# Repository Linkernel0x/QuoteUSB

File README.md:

# QuoteUSB

A small 3-button USB MacroPad built for HackClub as a hardware experiment with the CH552G microcontroller

---

- **Microcontroller:** CH552G
- **Inputs:** 3 switches (Quote Generator 1, Quote Generator 2, Macro button)
- **Status:** Integrated LED indicator on keypress

For the full devlog and project history, check out [JOURNAL.md](JOURNAL.md).

### Firmware
1. Open `firmware/firmware.ino` in Arduino IDE
2. Select **CH552 Board** and upload method **USER CODE w/ 148B USB ram** using the ch55xduino core
3. Flash the CH552

### BOM
| Reference   | Qty | Value    | Footprint                                            | Datasheet                                                                                        |
|:------------|:----|:---------|:-----------------------------------------------------|:-------------------------------------------------------------------------------------------------|
| C1,C2       | 2   | 100nf    | Capacitor\_SMD:C\_0805\_2012Metric                   | \~                                                                                               |
| D1          | 1   | LED      | LED\_SMD:LED\_0805\_2012Metric                       | \~                                                                                               |
| J1          | 1   | USB\_A   | Connector\_USB:USB\_A\_Molex\_48037-2200\_Horizontal | \~                                                                                               |
| R1          | 1   | 330R     | Resistor\_SMD:R\_0805\_2012Metric                    | \~                                                                                               |
| SW1,SW2,SW3 | 3   | SW\_Push | Button\_Switch\_SMD:SW\_SPST\_PTS645Sx43SMTR92       | \~                                                                                               |
| U1          | 1   | CH552G   | Package\_SO:SOIC-16\_3.9x9.9mm\_P1.27mm              | https://github.com/WeActStudio/WeActStudio.CH552CoreBoard/blob/master/Datasheet/CH552DS1\_en.PDF |

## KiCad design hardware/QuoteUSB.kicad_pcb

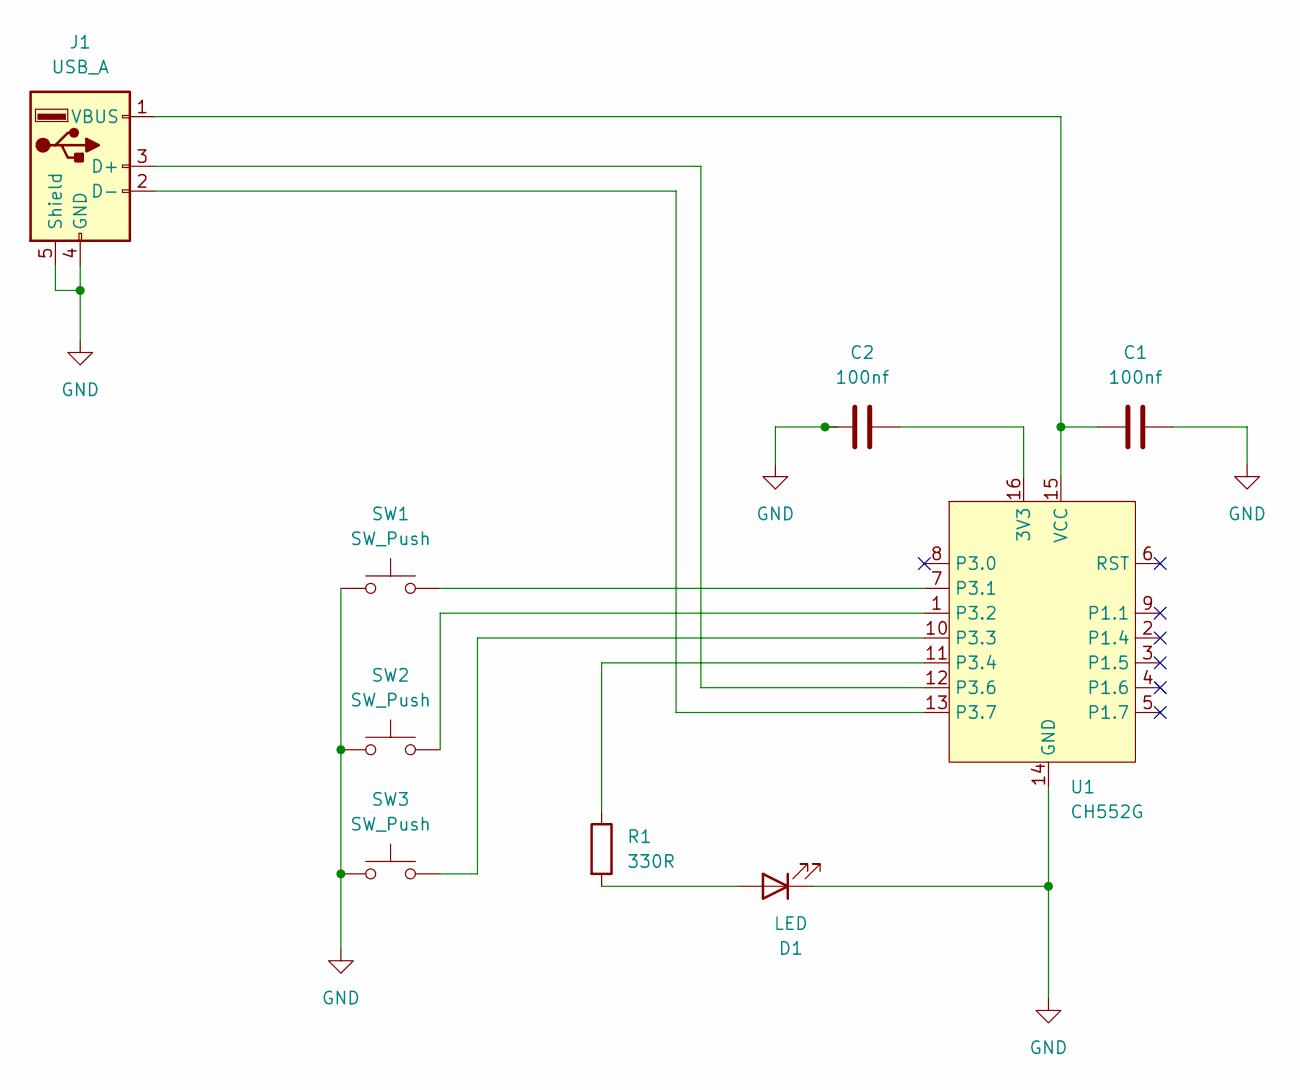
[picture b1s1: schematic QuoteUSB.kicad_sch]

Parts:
C1, C2: 100nf; C_0805_2012Metric
D1: LED; LED_0805_2012Metric
J1: USB_A; USB_A_Molex_48037-2200_Horizontal
R1: 330R; R_0805_2012Metric
SW1, SW2, SW3: SW_Push; SW_SPST_PTS645Sx43SMTR92
U1: CH552G; SOIC-16_3.9x9.9mm_P1.27mm

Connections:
GND: C1.2, C2.1, D1.1 (K), J1.4 (GND), J1.5 (Shield), SW1.1, SW2.1, SW3.1, U1.14 (GND)
unnamed: D1.2 (A), R1.2
unnamed: J1.3 (D+), U1.12 (P3.6)
unnamed: J1.2 (D-), U1.13 (P3.7)
unnamed: C1.1, J1.1 (VBUS), U1.15 (VCC)
unnamed: C2.2, U1.16 (3V3)
unnamed: SW1.2, U1.7 (P3.1)
unnamed: SW2.2, U1.1 (P3.2)
unnamed: SW3.2, U1.10 (P3.3)
unnamed: R1.1, U1.11 (P3.4)

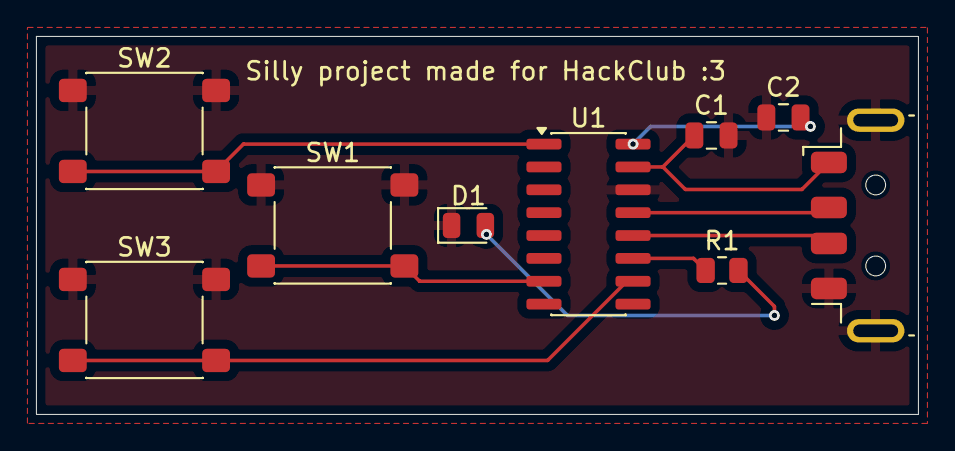
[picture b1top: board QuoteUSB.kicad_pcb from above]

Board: 2 copper layers, 49.0 x 21.0 mm, 9 parts (0 on the bottom side), 10 nets.

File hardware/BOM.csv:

"Reference","Qty","Value","DNP","Exclude from BOM","Exclude from Board","Footprint","Datasheet"
"C1,C2","2","100nf","","","","Capacitor_SMD:C_0805_2012Metric","~"
"D1","1","LED","","","","LED_SMD:LED_0805_2012Metric","~"
"J1","1","USB_A","","","","Connector_USB:USB_A_Molex_48037-2200_Horizontal","~"
"R1","1","330R","","","","Resistor_SMD:R_0805_2012Metric","~"
"SW1,SW2,SW3","3","SW_Push","","","","Button_Switch_SMD:SW_SPST_PTS645Sx43SMTR92","~"
"U1","1","CH552G","","","","Package_SO:SOIC-16_3.9x9.9mm_P1.27mm","https://github.com/WeActStudio/WeActStudio.CH552CoreBoard/bl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"
